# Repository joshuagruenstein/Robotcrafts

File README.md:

# Robotcrafts

Robotcrafts (working title) is a low cost "arts &amp; crafts" style kit for remote control robots.  The first prototype was created in the summer of 2015 for a robotics elective at [Camp Good Grief](https://www.eeh.org/bereavement/camp-good-grief/) at [East End Hospice](https://www.eeh.org/) in Southold, NY.  This repository covers all future versions of this concept, from 2016 onwards.

## Concept

The kit is comprised of a controller, motors, wheels, and standard arts &amp; crafts materials such as foamcore, double sided tape, and popsicle sticks.  The controller is a dual layer PCB with four pushbuttons, three AA batteries, and copper pads to attach the motor wires via alligator clips.   The motors are given to the children with 5ft of twisted leads attached to them, terminated with alligator clips.  All the kids have to do is clip the alligator clips onto the controller, allowing them to use the buttons to move the motors forwards and backwards.  

This design gives kids the freedom to experiment with different robot designs using existing arts and crafts skills, as it removes the challenge of wiring up a robot.  However, the electronics are still both simple enough to understand and cheap enough to give a robot per child: the goal is to price each kit at ~$10.  While this may not be economically feasible for every application, it's obviously still ideal to get kits such as these in the hands of as many kids as possible.

## Implementation

The current implementation uses a Toshiba TB6612FNG dual brushed motor controller and Dagu gearmotors and wheels.  The controller PCB is in EagleCAD, which while not being free software seems to be the standard over KiCAD for hobbyists, making it more "open" to the community.  These parts were chosen for their low price at the required scale.

An issue with the current implementation is ease of manufacturing: the process of soldering leads to the motors, applying hot glue for strain relief, attaching alligator clips, and soldering DIP and SMD parts to the PCB is quite laborious, especially in large quantities.  Last summer I spent a full day assembling ~25 kits of lesser complexity.  I'm not quite sure what to do about this at the moment except to allot more time for assembly, so if you have an idea please submit an issue or pull request.

## Photos

Below are some fun pictures of some of the robots kids at Camp Good Grief made last summer:

## Contributing

Please feel free to contribute, whether it be to suggest a feature or design change, update a schematic, or add pictures of a robot you've made!  Just submit either an issue or a pull request.

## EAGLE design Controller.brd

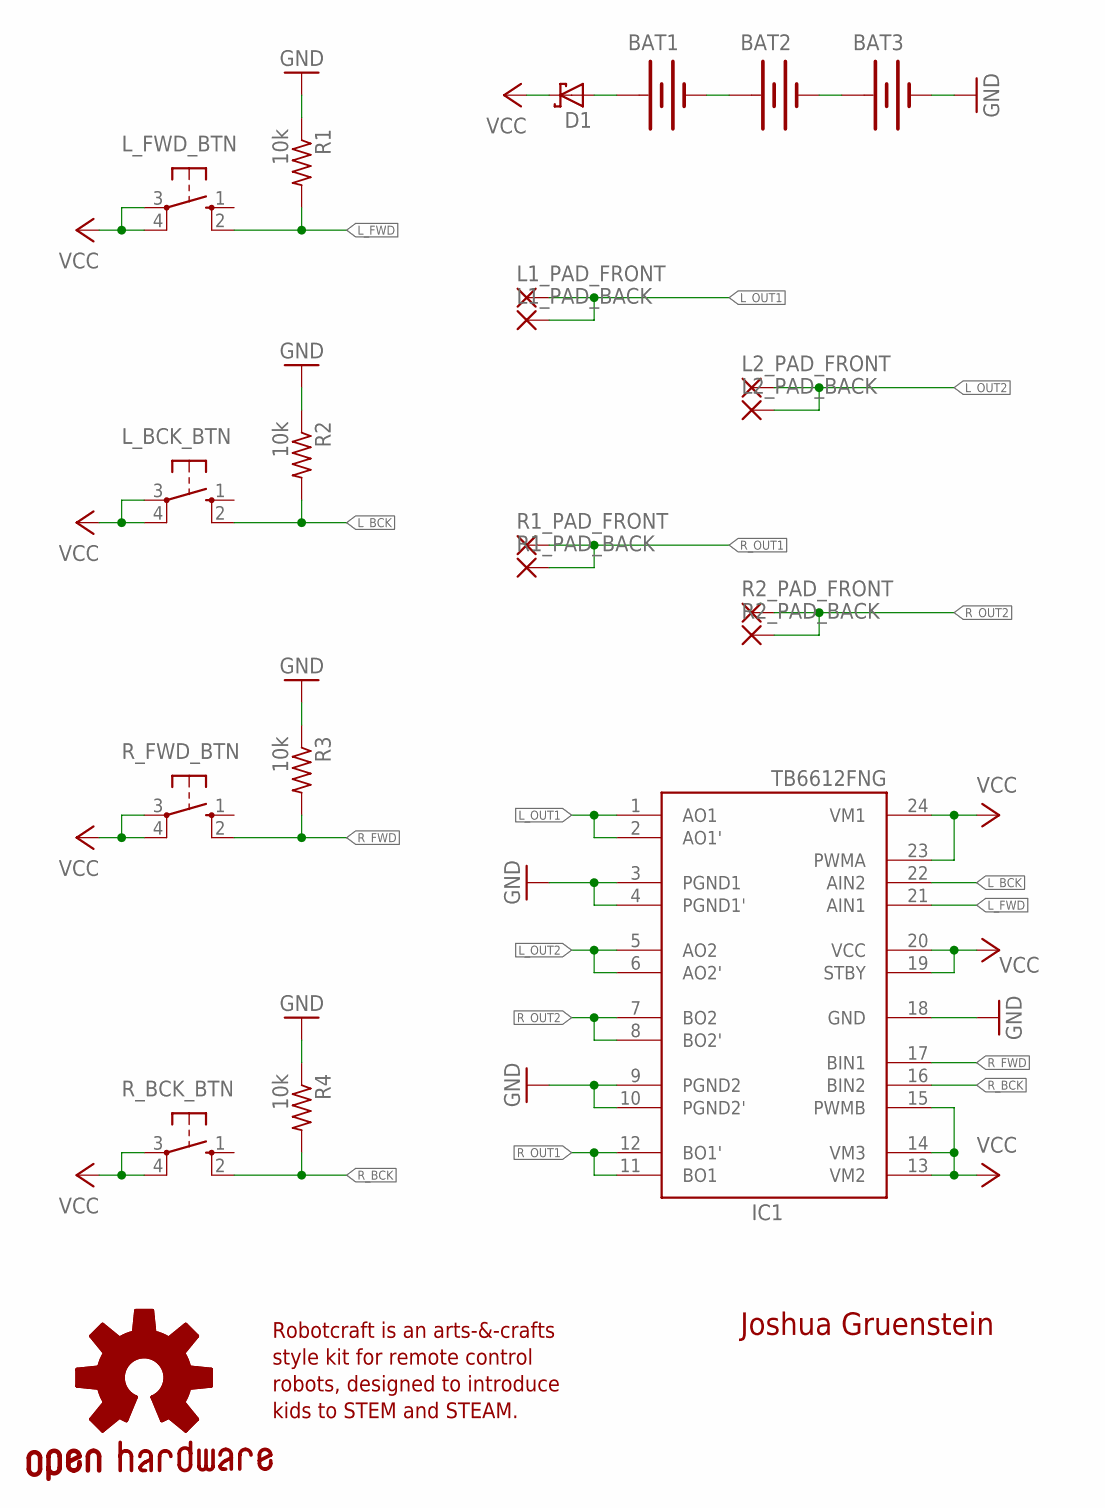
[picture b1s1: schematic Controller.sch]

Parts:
BAT1, BAT2, BAT3: BATTERYAA-KIT; BATTERY-AA-KIT
D1: SCHOTTKY-DIODESMC; SMC
GOLD_ORB_SM1: OSHWLOGO_GOLD_ORB_MED; OSHW1
IC1: TB6612FNG; SSOP24
L1_PAD_BACK, L1_PAD_FRONT, L2_PAD_BACK, L2_PAD_FRONT: WIREPADSMD5-2,5; 5-2,5
L_BCK_BTN: 40-XX; B3F-40XX
L_FWD_BTN: 40-XX; B3F-40XX
R1, R2, R3, R4: 10k; R0805
R1_PAD_BACK, R1_PAD_FRONT, R2_PAD_BACK, R2_PAD_FRONT: WIREPADSMD5-2,5; 5-2,5
R_BCK_BTN: 40-XX; B3F-40XX
R_FWD_BTN: 40-XX; B3F-40XX

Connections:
GND: BAT3.GND@1 (-), IC1.3 (PGND1), IC1.4 (PGND1'), IC1.9 (PGND2), IC1.10 (PGND2'), IC1.18 (GND), R1.1, R2.1, R3.1, R4.1
L_BCK: IC1.22 (AIN2), L_BCK_BTN.2 (S1), R2.2
L_FWD: IC1.21 (AIN1), L_FWD_BTN.2 (S1), R1.2
L_OUT1: IC1.1 (AO1), IC1.2 (AO1'), L1_PAD_BACK.1, L1_PAD_FRONT.1
L_OUT2: IC1.5 (AO2), IC1.6 (AO2'), L2_PAD_BACK.1, L2_PAD_FRONT.1
unnamed: BAT1.GND@1 (-), BAT2.PWR@1 (+)
unnamed: BAT2.GND@1 (-), BAT3.PWR@1 (+)
unnamed: BAT1.PWR@1 (+), D1.A
R_BCK: IC1.16 (BIN2), R4.2, R_BCK_BTN.2 (S1)
R_FWD: IC1.17 (BIN1), R3.2, R_FWD_BTN.2 (S1)
R_OUT1: IC1.11 (BO1), IC1.12 (BO1'), R1_PAD_BACK.1, R1_PAD_FRONT.1
R_OUT2: IC1.7 (BO2), IC1.8 (BO2'), R2_PAD_BACK.1, R2_PAD_FRONT.1
VCC: D1.C, IC1.13 (VM2), IC1.14 (VM3), IC1.15 (PWMB), IC1.19 (STBY), IC1.20 (VCC), IC1.23 (PWMA), IC1.24 (VM1), L_BCK_BTN.3, L_BCK_BTN.4 (P1), L_FWD_BTN.3, L_FWD_BTN.4 (P1), R_BCK_BTN.3, R_BCK_BTN.4 (P1), R_FWD_BTN.3, R_FWD_BTN.4 (P1)

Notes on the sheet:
Joshua Gruenstein
Robotcraft is an arts-&-crafts style kit for remote control robots, designed to introduce kids to STEM and STEAM.

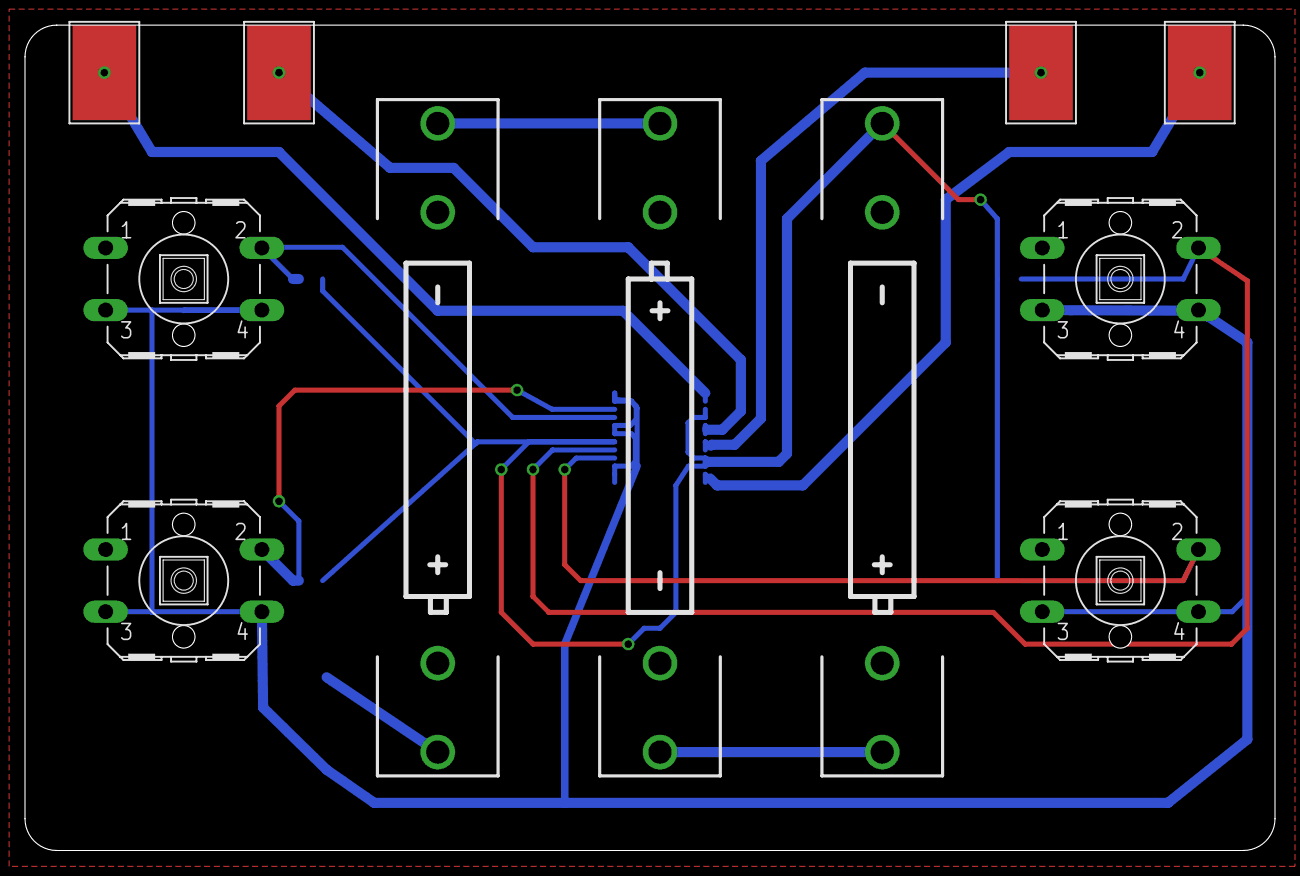
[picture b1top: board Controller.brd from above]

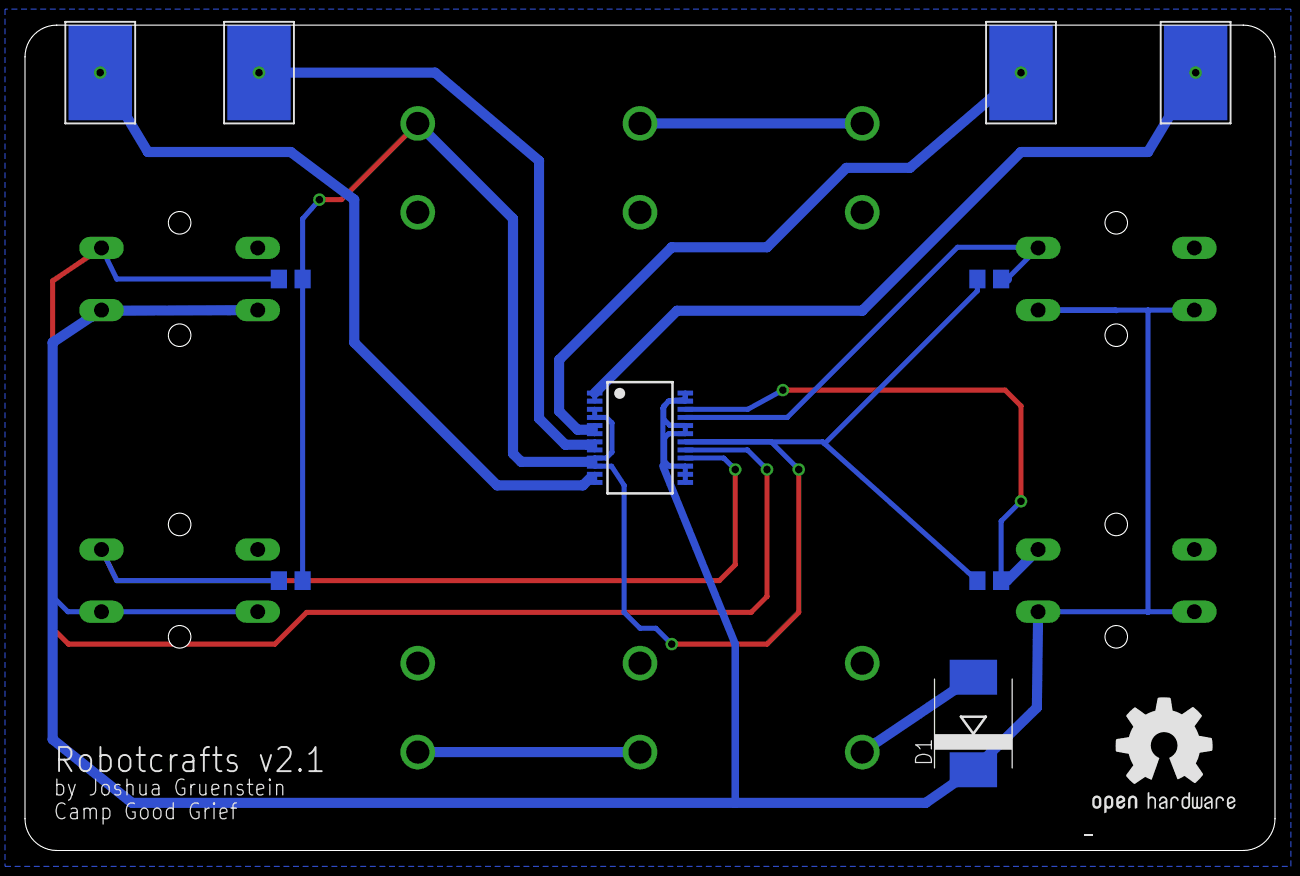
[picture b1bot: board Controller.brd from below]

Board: 2 copper layers, 100.0 x 66.0 mm, 22 parts (11 on the bottom side), 13 nets.

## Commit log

2016-06-22 add bill of materials
2016-06-22 initial controller schematic
2016-06-22 update MIT license to hardware-specific language
2016-06-22 add content to readme
2016-06-27 add motor pads
2016-06-27 add fancy A5 portrait frame to schematic
2016-06-27 initial board component layout
2016-07-06 initial board routing
2016-07-06 add ground copper fills
2016-07-06 board version + author silkscreen
2016-07-06 v0.1 gerber files
2016-07-06 adjust silkscreen
2016-07-06 update BOM
2016-07-12 pcb rounded corners
2016-07-14 cosmetic PCB upgrades
    added OSHW logo to bottom silkscreen
2016-07-14 enlarge board alligator pad size
2016-07-22 fix button alignment
    in other news, I got the 0.2 PCBs back today and they are **gorgeous**
2017-05-08 add diode to board and schematic

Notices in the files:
parts and their libraries:
SparkFun-Electromechanical: Licensing: Creative Commons ShareAlike 4.0 International - https://creativecommons.org/licenses/by-sa/4.0
